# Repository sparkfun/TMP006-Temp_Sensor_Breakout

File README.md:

**NOTE:** *This product has been retired from our catalog. If you are looking for more up-to-date info, please check out some of these resources to see how other users are still hacking and improving on this product.*
* *[SparkFun Forum](https://forum.sparkfun.com/)*
* *[Comments Here on GitHub](https://github.com/sparkfun/TMP006-Temp_Sensor_Breakout/issues)*
* *[IRC Channel](https://www.sparkfun.com/news/263)*

TMP006-Temp Sensor Breakout
===========================
[  
*TMP006 Breakout (SEN-11859)*](https://www.sparkfun.com/products/11859)

This breakout board for the TMP006 sensor allows you to measure the temperature of an object without making contact. 

Repository Contents
-------------------
* **/Firmware** - Example Arduino firmware to work with this 
* **/Hardware** - Eagle PCB layout files
* **/Production** - Test bed files and production panel files

Documentation
-------------------
* [Hookup Guide](https://learn.sparkfun.com/tutorials/tmp006-hookup-guide) - Basic hookup guide for the TMP006.

Version History
---------------
* [vH11](https://github.com/sparkfun/TMP006-Temp_Sensor_Breakout/releases/tag/v_1.1) - Second production run.
* [vH10](https://github.com/sparkfun/TMP006-Temp_Sensor_Breakout/releases/tag/v_1.0) -  First production run.
* vH01 - First protoboard run.

License Information
-------------------
The hardware is released under [Creative Commons Share-alike 3.0](http://creativecommons.org/licenses/by-sa/3.0/).  
All other code is open source so please feel free to do anything you want with it; you buy me a beer if you use this and we meet someday ([Beerware license](http://en.wikipedia.org/wiki/Beerware)).

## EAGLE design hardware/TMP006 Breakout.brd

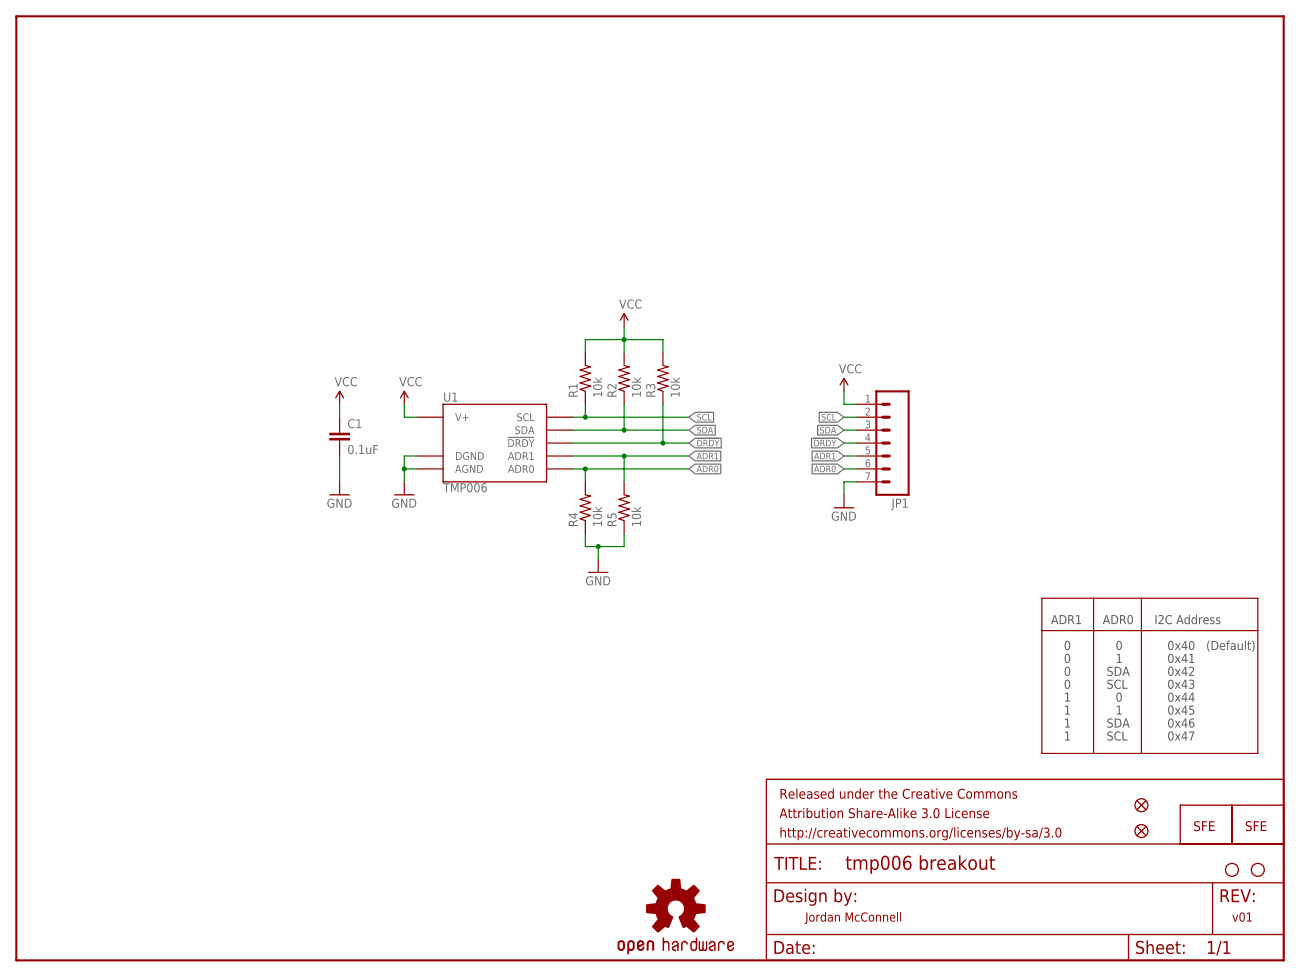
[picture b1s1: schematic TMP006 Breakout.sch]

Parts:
C1: 0.1uF; 0603-CAP
FID1, FID2: FIDUCIALUFIDUCIAL; MICRO-FIDUCIAL
FRAME1: FRAME-LETTER; CREATIVE_COMMONS
JP1: M07; 1X07
LOGO1: LOGO-SFESK; SFE-LOGO-FLAME
LOGO2: OSHW-LOGOS; OSHW-LOGO-S
LOGO3: LOGO-SFENEW; SFE-NEW-WEBLOGO
R1, R2, R3, R4, R5: 10k; 0603-RES
STANDOFF1, STANDOFF2: STAND-OFF
U1: TMP006; BGA8DS

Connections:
!DRDY: JP1.4, R3.1, U1.C2 (!DRDY)
ADR0: JP1.6, R4.2, U1.C1 (ADR0)
ADR1: JP1.5, R5.2, U1.B1 (ADR1)
GND: C1.2, JP1.7, R4.1, R5.1, U1.A1 (DGND), U1.A2 (AGND)
SCL: JP1.2, R1.1, U1.B3 (SCL)
SDA: JP1.3, R2.1, U1.C3 (SDA)
VCC: C1.1, JP1.1, R1.2, R2.2, R3.2, U1.A3 (V+)

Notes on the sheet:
Jordan McConnell
v01
ADR1
ADR0
I2C Address
SDA
SCL
0x40
0x41
0x42
0x43
0x44
0x45
0x46
0x47
(Default)

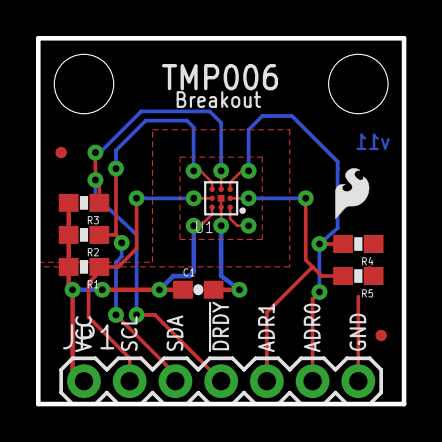
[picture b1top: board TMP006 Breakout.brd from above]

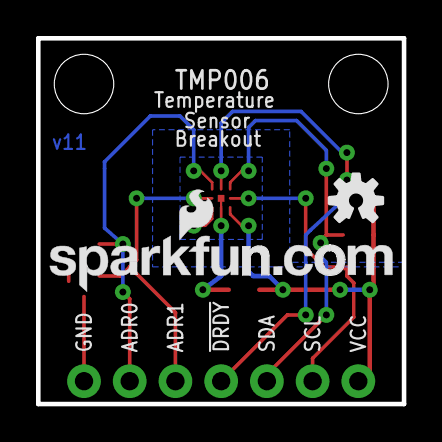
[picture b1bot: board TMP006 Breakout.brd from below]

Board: 2 copper layers, 20.3 x 20.3 mm, 16 parts (2 on the bottom side), 7 nets.

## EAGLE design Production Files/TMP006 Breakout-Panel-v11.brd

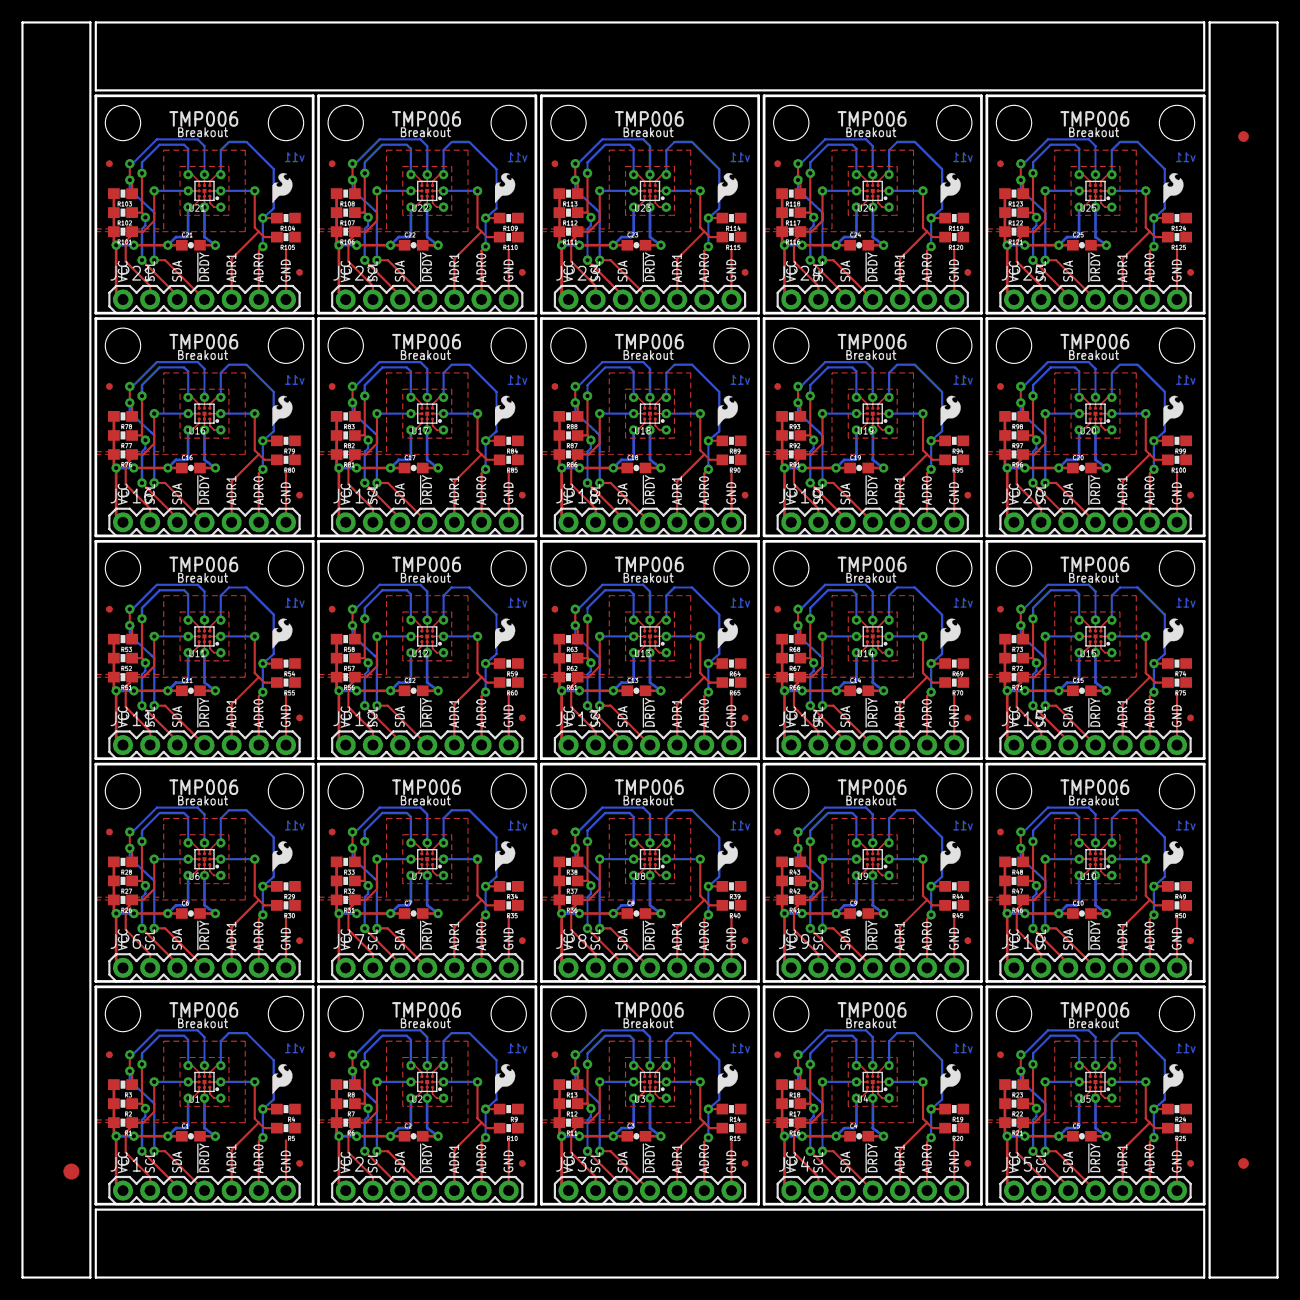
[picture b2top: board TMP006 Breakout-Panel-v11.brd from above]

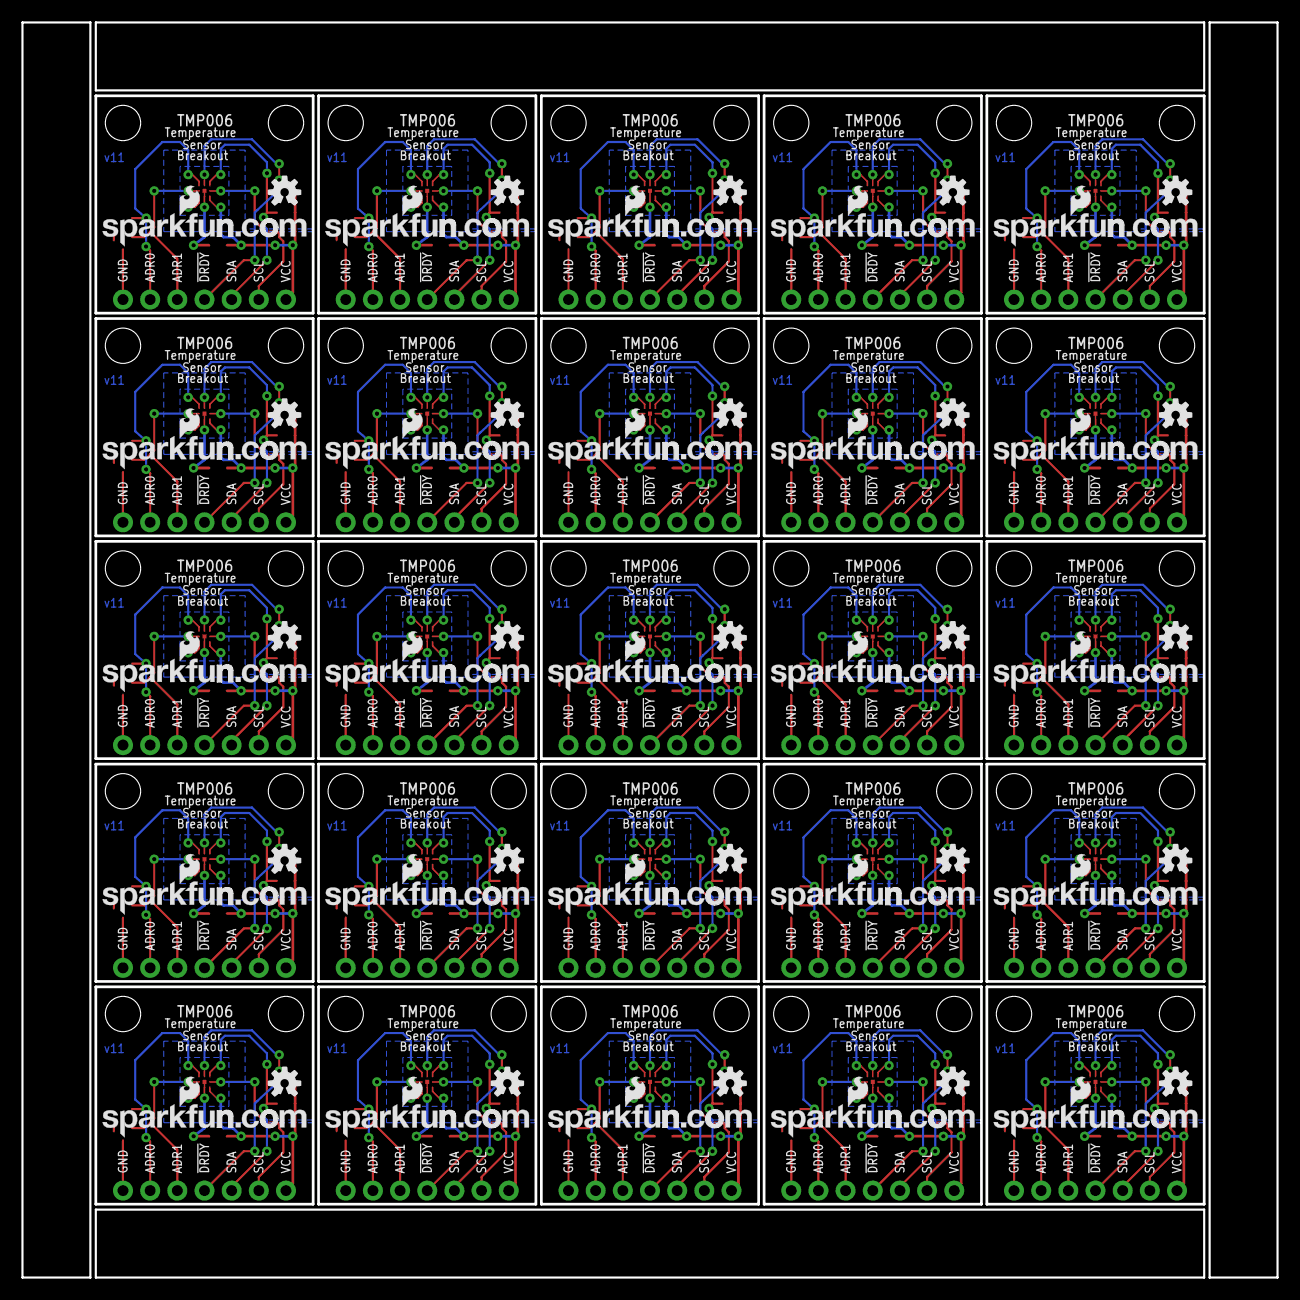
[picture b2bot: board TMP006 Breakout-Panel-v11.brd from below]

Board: 2 copper layers, 117.3 x 117.3 mm, 378 parts (50 on the bottom side), 175 nets.

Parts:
C1, C2, C3, C4, C5, C6, C7, C8, C9, C10, C11, C12, C13, C14, C15, C16, C17, C18, C19, C20, C21, C22, C23, C24, C25: 0.1uF; 0603-CAP
E$1: FIDUCIAL-1.5X3
E$4, E$5: FIDUCIAL-1X2
FID1, FID2, FID3, FID4, FID5, FID6, FID7, FID8, FID9, FID10, FID11, FID12, FID13, FID14, FID15, FID16, FID17, FID18, FID19, FID20, FID21, FID22, FID23, FID24, FID25, FID26, FID27, FID28, FID29, FID30, FID31, FID32, FID33, FID34, FID35, FID36, FID37, FID38, FID39, FID40, FID41, FID42, FID43, FID44, FID45, FID46, FID47, FID48, FID49, FID50: FIDUCIALUFIDUCIAL; MICRO-FIDUCIAL
JP1, JP2, JP3, JP4, JP5, JP6, JP7, JP8, JP9, JP10, JP11, JP12, JP13, JP14, JP15, JP16, JP17, JP18, JP19, JP20, JP21, JP22, JP23, JP24, JP25: 1X07
LOGO1, LOGO4, LOGO7, LOGO10, LOGO13, LOGO16, LOGO19, LOGO22, LOGO25, LOGO28, LOGO31, LOGO34, LOGO37, LOGO40, LOGO43, LOGO46, LOGO49, LOGO52, LOGO55, LOGO58, LOGO61, LOGO64, LOGO67, LOGO70, LOGO73: LOGO-SFESK; SFE-LOGO-FLAME
LOGO2, LOGO5, LOGO8, LOGO11, LOGO14, LOGO17, LOGO20, LOGO23, LOGO26, LOGO29, LOGO32, LOGO35, LOGO38, LOGO41, LOGO44, LOGO47, LOGO50, LOGO53, LOGO56, LOGO59, LOGO62, LOGO65, LOGO68, LOGO71, LOGO74: OSHW-LOGOS; OSHW-LOGO-S
LOGO3, LOGO6, LOGO9, LOGO12, LOGO15, LOGO18, LOGO21, LOGO24, LOGO27, LOGO30, LOGO33, LOGO36, LOGO39, LOGO42, LOGO45, LOGO48, LOGO51, LOGO54, LOGO57, LOGO60, LOGO63, LOGO66, LOGO69, LOGO72, LOGO75: LOGO-SFENEW; SFE-NEW-WEBLOGO
R1, R2, R3, R4, R5, R6, R7, R8, R9, R10, R11, R12, R13, R14, R15, R16, R17, R18, R19, R20, R21, R22, R23, R24, R25, R26, R27, R28, R29, R30, R31, R32, R33, R34, R35, R36, R37, R38, R39, R40, R41, R42, R43, R44, R45, R46, R47, R48, R49, R50, R51, R52, R53, R54, R55, R56, R57, R58, R59, R60, R61, R62, R63, R64, R65, R66, R67, R68, R69, R70, R71, R72, R73, R74, R75, R76, R77, R78, R79, R80, R81, R82, R83, R84, R85, R86, R87, R88, R89, R90, R91, R92, R93, R94, R95, R96, R97, R98, R99, R100, R101, R102, R103, R104, R105, R106, R107, R108, R109, R110, R111, R112, R113, R114, R115, R116, R117, R118, R119, R120, R121, R122, R123, R124, R125: 10k; 0603-RES
STANDOFF1, STANDOFF2, STANDOFF3, STANDOFF4, STANDOFF5, STANDOFF6, STANDOFF7, STANDOFF8, STANDOFF9, STANDOFF10, STANDOFF11, STANDOFF12, STANDOFF13, STANDOFF14, STANDOFF15, STANDOFF16, STANDOFF17, STANDOFF18, STANDOFF19, STANDOFF20, STANDOFF21, STANDOFF22, STANDOFF23, STANDOFF24, STANDOFF25, STANDOFF26, STANDOFF27, STANDOFF28, STANDOFF29, STANDOFF30, STANDOFF31, STANDOFF32, STANDOFF33, STANDOFF34, STANDOFF35, STANDOFF36, STANDOFF37, STANDOFF38, STANDOFF39, STANDOFF40, STANDOFF41, STANDOFF42, STANDOFF43, STANDOFF44, STANDOFF45, STANDOFF46, STANDOFF47, STANDOFF48, STANDOFF49, STANDOFF50: STAND-OFF
U1, U2, U3, U4, U5, U6, U7, U8, U9, U10, U11, U12, U13, U14, U15, U16, U17, U18, U19, U20, U21, U22, U23, U24, U25: TMP006; BGA8DS

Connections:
!DRDY: JP1.4, R3.1, U1.C2
!DRDY1: JP2.4, R8.1, U2.C2
!DRDY2: JP3.4, R13.1, U3.C2
!DRDY3: JP4.4, R18.1, U4.C2
!DRDY4: JP5.4, R23.1, U5.C2
!DRDY5: JP6.4, R28.1, U6.C2
!DRDY6: JP7.4, R33.1, U7.C2
!DRDY7: JP8.4, R38.1, U8.C2
!DRDY8: JP9.4, R43.1, U9.C2
!DRDY9: JP10.4, R48.1, U10.C2
!DRDY10: JP11.4, R53.1, U11.C2
!DRDY11: JP12.4, R58.1, U12.C2
!DRDY12: JP13.4, R63.1, U13.C2
!DRDY13: JP14.4, R68.1, U14.C2
!DRDY14: JP15.4, R73.1, U15.C2
!DRDY15: JP16.4, R78.1, U16.C2
!DRDY16: JP17.4, R83.1, U17.C2
!DRDY17: JP18.4, R88.1, U18.C2
!DRDY18: JP19.4, R93.1, U19.C2
!DRDY19: JP20.4, R98.1, U20.C2
!DRDY20: JP21.4, R103.1, U21.C2
!DRDY21: JP22.4, R108.1, U22.C2
!DRDY22: JP23.4, R113.1, U23.C2
!DRDY23: JP24.4, R118.1, U24.C2
!DRDY24: JP25.4, R123.1, U25.C2
ADR0: JP1.6, R4.2, U1.C1
ADR1: JP1.5, R5.2, U1.B1
ADR2: JP2.6, R9.2, U2.C1
ADR3: JP2.5, R10.2, U2.B1
ADR4: JP3.6, R14.2, U3.C1
ADR5: JP3.5, R15.2, U3.B1
ADR6: JP4.6, R19.2, U4.C1
ADR7: JP4.5, R20.2, U4.B1
ADR8: JP5.6, R24.2, U5.C1
ADR9: JP5.5, R25.2, U5.B1
ADR10: JP6.6, R29.2, U6.C1
ADR11: JP6.5, R30.2, U6.B1
ADR12: JP7.6, R34.2, U7.C1
ADR13: JP7.5, R35.2, U7.B1
ADR14: JP8.6, R39.2, U8.C1
ADR15: JP8.5, R40.2, U8.B1
ADR16: JP9.6, R44.2, U9.C1
ADR17: JP9.5, R45.2, U9.B1
ADR18: JP10.6, R49.2, U10.C1
ADR19: JP10.5, R50.2, U10.B1
ADR20: JP11.6, R54.2, U11.C1
ADR21: JP11.5, R55.2, U11.B1
ADR22: JP12.6, R59.2, U12.C1
ADR23: JP12.5, R60.2, U12.B1
ADR24: JP13.6, R64.2, U13.C1
ADR25: JP13.5, R65.2, U13.B1
ADR26: JP14.6, R69.2, U14.C1
ADR27: JP14.5, R70.2, U14.B1
ADR28: JP15.6, R74.2, U15.C1
ADR29: JP15.5, R75.2, U15.B1
ADR30: JP16.6, R79.2, U16.C1
ADR31: JP16.5, R80.2, U16.B1
ADR32: JP17.6, R84.2, U17.C1
ADR33: JP17.5, R85.2, U17.B1
ADR34: JP18.6, R89.2, U18.C1
ADR35: JP18.5, R90.2, U18.B1
ADR36: JP19.6, R94.2, U19.C1
ADR37: JP19.5, R95.2, U19.B1
ADR38: JP20.6, R99.2, U20.C1
ADR39: JP20.5, R100.2, U20.B1
ADR40: JP21.6, R104.2, U21.C1
ADR41: JP21.5, R105.2, U21.B1
ADR42: JP22.6, R109.2, U22.C1
ADR43: JP22.5, R110.2, U22.B1
ADR44: JP23.6, R114.2, U23.C1
ADR45: JP23.5, R115.2, U23.B1
ADR46: JP24.6, R119.2, U24.C1
ADR47: JP24.5, R120.2, U24.B1
ADR48: JP25.6, R124.2, U25.C1
ADR49: JP25.5, R125.2, U25.B1
GND: C1.2, JP1.7, R4.1, R5.1, U1.A1, U1.A2
GND1: C2.2, JP2.7, R9.1, R10.1, U2.A1, U2.A2
GND2: C3.2, JP3.7, R14.1, R15.1, U3.A1, U3.A2
GND3: C4.2, JP4.7, R19.1, R20.1, U4.A1, U4.A2
GND4: C5.2, JP5.7, R24.1, R25.1, U5.A1, U5.A2
GND5: C6.2, JP6.7, R29.1, R30.1, U6.A1, U6.A2
GND6: C7.2, JP7.7, R34.1, R35.1, U7.A1, U7.A2
GND7: C8.2, JP8.7, R39.1, R40.1, U8.A1, U8.A2
GND8: C9.2, JP9.7, R44.1, R45.1, U9.A1, U9.A2
GND9: C10.2, JP10.7, R49.1, R50.1, U10.A1, U10.A2
GND10: C11.2, JP11.7, R54.1, R55.1, U11.A1, U11.A2
GND11: C12.2, JP12.7, R59.1, R60.1, U12.A1, U12.A2
GND12: C13.2, JP13.7, R64.1, R65.1, U13.A1, U13.A2
GND13: C14.2, JP14.7, R69.1, R70.1, U14.A1, U14.A2
GND14: C15.2, JP15.7, R74.1, R75.1, U15.A1, U15.A2
GND15: C16.2, JP16.7, R79.1, R80.1, U16.A1, U16.A2
GND16: C17.2, JP17.7, R84.1, R85.1, U17.A1, U17.A2
GND17: C18.2, JP18.7, R89.1, R90.1, U18.A1, U18.A2
GND18: C19.2, JP19.7, R94.1, R95.1, U19.A1, U19.A2
GND19: C20.2, JP20.7, R99.1, R100.1, U20.A1, U20.A2
GND20: C21.2, JP21.7, R104.1, R105.1, U21.A1, U21.A2
GND21: C22.2, JP22.7, R109.1, R110.1, U22.A1, U22.A2
GND22: C23.2, JP23.7, R114.1, R115.1, U23.A1, U23.A2
GND23: C24.2, JP24.7, R119.1, R120.1, U24.A1, U24.A2
GND24: C25.2, JP25.7, R124.1, R125.1, U25.A1, U25.A2
SCL: JP1.2, R1.1, U1.B3
SCL1: JP2.2, R6.1, U2.B3
SCL2: JP3.2, R11.1, U3.B3
SCL3: JP4.2, R16.1, U4.B3
SCL4: JP5.2, R21.1, U5.B3
SCL5: JP6.2, R26.1, U6.B3
SCL6: JP7.2, R31.1, U7.B3
SCL7: JP8.2, R36.1, U8.B3
SCL8: JP9.2, R41.1, U9.B3
SCL9: JP10.2, R46.1, U10.B3
SCL10: JP11.2, R51.1, U11.B3
SCL11: JP12.2, R56.1, U12.B3
SCL12: JP13.2, R61.1, U13.B3
SCL13: JP14.2, R66.1, U14.B3
SCL14: JP15.2, R71.1, U15.B3
SCL15: JP16.2, R76.1, U16.B3
SCL16: JP17.2, R81.1, U17.B3
SCL17: JP18.2, R86.1, U18.B3
SCL18: JP19.2, R91.1, U19.B3
SCL19: JP20.2, R96.1, U20.B3
SCL20: JP21.2, R101.1, U21.B3
SCL21: JP22.2, R106.1, U22.B3
SCL22: JP23.2, R111.1, U23.B3
SCL23: JP24.2, R116.1, U24.B3
SCL24: JP25.2, R121.1, U25.B3
SDA: JP1.3, R2.1, U1.C3
SDA1: JP2.3, R7.1, U2.C3
SDA2: JP3.3, R12.1, U3.C3
SDA3: JP4.3, R17.1, U4.C3
SDA4: JP5.3, R22.1, U5.C3
SDA5: JP6.3, R27.1, U6.C3
SDA6: JP7.3, R32.1, U7.C3
SDA7: JP8.3, R37.1, U8.C3
SDA8: JP9.3, R42.1, U9.C3
SDA9: JP10.3, R47.1, U10.C3
SDA10: JP11.3, R52.1, U11.C3
SDA11: JP12.3, R57.1, U12.C3
SDA12: JP13.3, R62.1, U13.C3
SDA13: JP14.3, R67.1, U14.C3
SDA14: JP15.3, R72.1, U15.C3
SDA15: JP16.3, R77.1, U16.C3
SDA16: JP17.3, R82.1, U17.C3
SDA17: JP18.3, R87.1, U18.C3
SDA18: JP19.3, R92.1, U19.C3
SDA19: JP20.3, R97.1, U20.C3
SDA20: JP21.3, R102.1, U21.C3
SDA21: JP22.3, R107.1, U22.C3
SDA22: JP23.3, R112.1, U23.C3
SDA23: JP24.3, R117.1, U24.C3
SDA24: JP25.3, R122.1, U25.C3
VCC: C1.1, JP1.1, R1.2, R2.2, R3.2, U1.A3
VCC1: C2.1, JP2.1, R6.2, R7.2, R8.2, U2.A3
VCC2: C3.1, JP3.1, R11.2, R12.2, R13.2, U3.A3
VCC3: C4.1, JP4.1, R16.2, R17.2, R18.2, U4.A3
VCC4: C5.1, JP5.1, R21.2, R22.2, R23.2, U5.A3
VCC5: C6.1, JP6.1, R26.2, R27.2, R28.2, U6.A3
VCC6: C7.1, JP7.1, R31.2, R32.2, R33.2, U7.A3
VCC7: C8.1, JP8.1, R36.2, R37.2, R38.2, U8.A3
VCC8: C9.1, JP9.1, R41.2, R42.2, R43.2, U9.A3
VCC9: C10.1, JP10.1, R46.2, R47.2, R48.2, U10.A3
VCC10: C11.1, JP11.1, R51.2, R52.2, R53.2, U11.A3
VCC11: C12.1, JP12.1, R56.2, R57.2, R58.2, U12.A3
VCC12: C13.1, JP13.1, R61.2, R62.2, R63.2, U13.A3
VCC13: C14.1, JP14.1, R66.2, R67.2, R68.2, U14.A3
VCC14: C15.1, JP15.1, R71.2, R72.2, R73.2, U15.A3
VCC15: C16.1, JP16.1, R76.2, R77.2, R78.2, U16.A3
VCC16: C17.1, JP17.1, R81.2, R82.2, R83.2, U17.A3
VCC17: C18.1, JP18.1, R86.2, R87.2, R88.2, U18.A3
VCC18: C19.1, JP19.1, R91.2, R92.2, R93.2, U19.A3
VCC19: C20.1, JP20.1, R96.2, R97.2, R98.2, U20.A3
VCC20: C21.1, JP21.1, R101.2, R102.2, R103.2, U21.A3
VCC21: C22.1, JP22.1, R106.2, R107.2, R108.2, U22.A3
VCC22: C23.1, JP23.1, R111.2, R112.2, R113.2, U23.A3
VCC23: C24.1, JP24.1, R116.2, R117.2, R118.2, U24.A3
VCC24: C25.1, JP25.1, R121.2, R122.2, R123.2, U25.A3

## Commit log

2013-05-10 Added v01 hardware.
2013-05-13 Updates to v01: 402 -> 603 packages, added trestrict, changed trace sizes.
2013-06-21 v10 hardware update
2013-06-24 Added I2C addresses on schematic, minor silk and board updates
2013-06-24 Production readied
    created panel
    added fiducials
2013-08-27 Adding firmware and gitignore, updating README
2013-08-30 Updating file licenses
2013-12-16 v11 ready
2013-12-18 Added Fiducials to the board and paneled it
2014-01-27 Removed „>“ on original code license note - breaks compiling: error: expected unqualified-id before '>' token
2014-10-17 fix for merge conflict
2017-11-28 Update README.md
    add hookup guide link
2018-08-15 Update I2C_functions.ino
    Remove `Wire.beginTransmission()` and `Wire.endTransmission()` based on issue [ [https://github.com/sparkfun/TMP006-Temp_Sensor_Breakout/issues/9](https://github.com/sparkfun/TMP006-Temp_Sensor_Break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

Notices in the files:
parts and their libraries:
SparkFun-Aesthetics: Licensing: CC v3.0 Share-Alike You are welcome to use this library for commercial purposes.
SparkFun-Aesthetics: Released under the Creative Commons Attribution Share-Alike 3.0 License
SparkFun-Aesthetics: Released under the Creative Commons
